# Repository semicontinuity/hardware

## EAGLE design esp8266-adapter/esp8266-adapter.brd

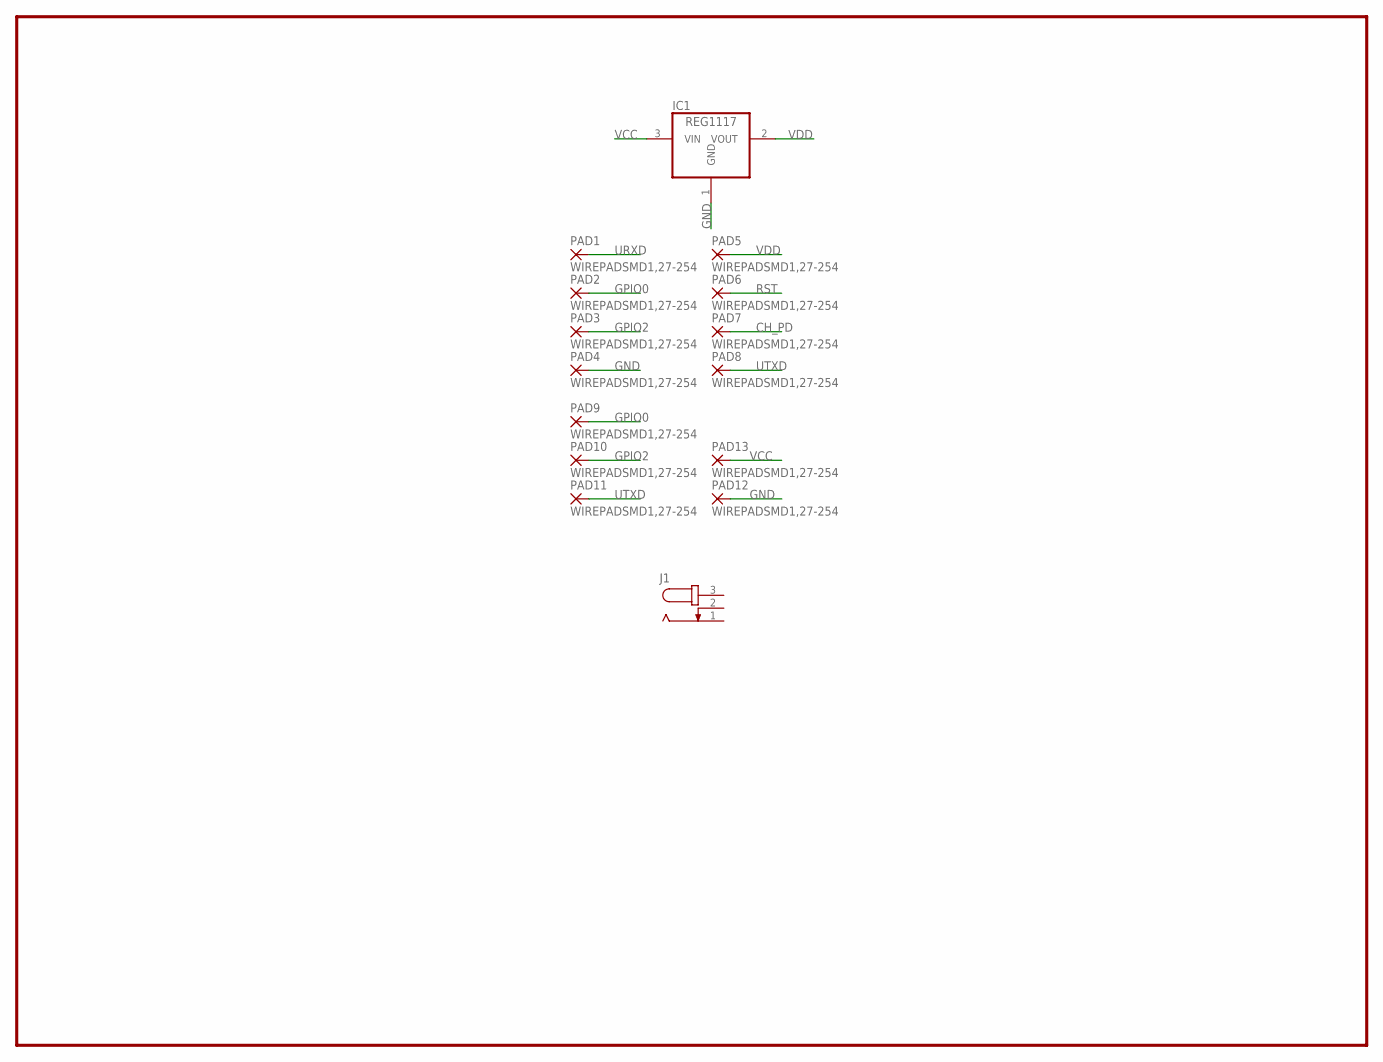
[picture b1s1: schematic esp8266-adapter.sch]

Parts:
IC1: REG1117; SOT223
J1: JACK-PLUG0; SPC4077
PAD1, PAD2, PAD3, PAD4, PAD5, PAD6, PAD7, PAD8, PAD9, PAD10, PAD11, PAD12, PAD13: WIREPADSMD1,27-254; SMD1,27-2,54

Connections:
CH_PD: PAD7.1
GND: IC1.1 (GND), PAD4.1, PAD12.1
GPIO0: PAD2.1, PAD9.1
GPIO2: PAD3.1, PAD10.1
RST: PAD6.1
URXD: PAD1.1
UTXD: PAD8.1, PAD11.1
VCC: IC1.3 (VIN), PAD13.1
VDD: IC1.2 (VOUT), PAD5.1

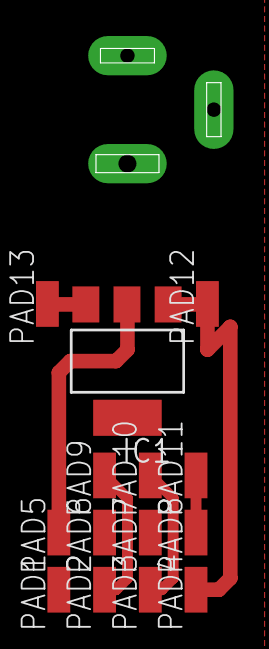
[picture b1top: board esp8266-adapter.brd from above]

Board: 2 copper layers, 15 parts (1 on the bottom side), 6 nets.

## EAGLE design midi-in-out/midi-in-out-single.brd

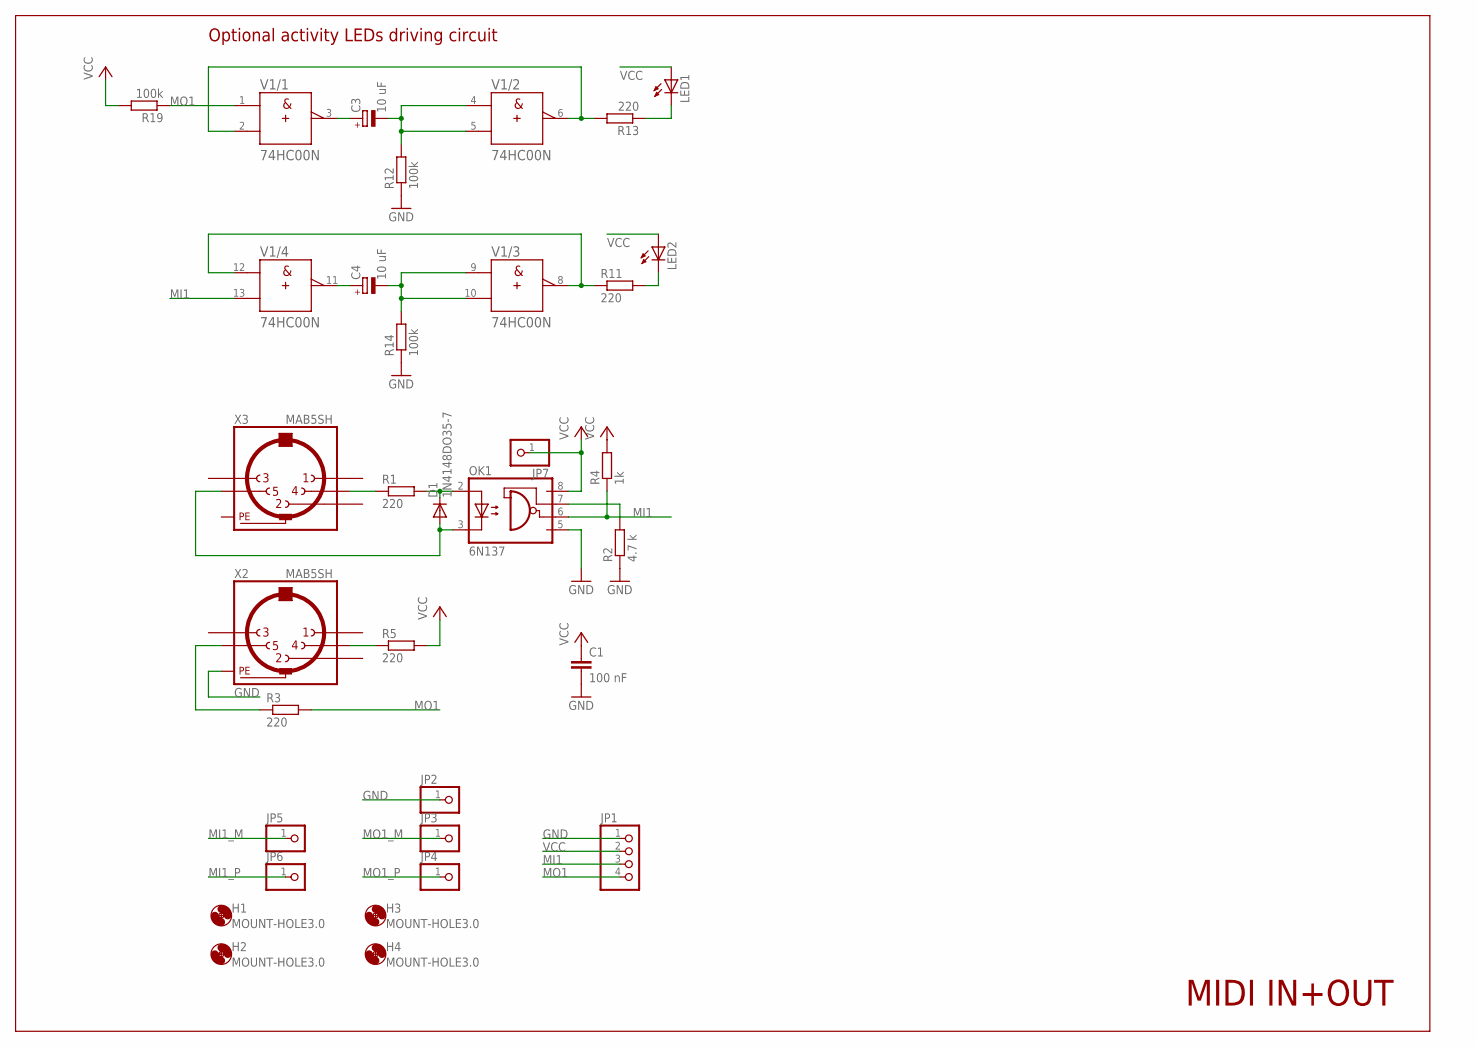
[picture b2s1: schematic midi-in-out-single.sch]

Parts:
C1: 100 nF; C025-024X044
C3, C4: 10 uF; E2,5-5
D1: 1N4148DO35-7; DO35-7
H1, H2, H3, H4: MOUNT-HOLE3.0; 3,0
JP1: PINHD-1X4/90; 1X04/90
JP2, JP3, JP4, JP5, JP6, JP7: PINHD-1X1; 1X01
LED1, LED2: LED3MM
OK1: 6N137; DIL08
R1, R3, R5, R11, R13: 220; 0204/7
R2: 4.7 k; 0204/7
R4: 1k; 0204/7
R12, R14, R19: 100k; 0204/7
V1: 74HC00N; DIL14
X2, X3: MAB5SH

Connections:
GND: C1.2, JP1.1, JP2.1, OK1.5 (GND), R2.1, R12.1, R14.1, V1.7 (-UB), X2.PE, X2.PE@ (PE)
MI1: JP1.3, OK1.6 (VO), R4.1, V1.13 (B)
MI1_M: D1.A, JP5.1, OK1.3 (C), X3.5
MI1_P: JP6.1, R1.1, X3.4
MO1: JP1.4, R3.2, R19.1, V1.1 (A)
MO1_M: JP3.1, R3.1, X2.5
MO1_P: JP4.1, R5.1, X2.4
unnamed: D1.C, OK1.2 (A), R1.2
unnamed: OK1.7 (VE), R2.2
unnamed: LED2.K (C), R11.2
unnamed: LED1.K (C), R13.1
unnamed: C4.+, V1.11 (Y)
unnamed: C3.-, R12.2, V1.4 (A), V1.5 (B)
unnamed: C3.+, V1.3 (Y)
unnamed: R13.2, V1.2 (B), V1.6 (Y)
unnamed: C4.-, R14.2, V1.9 (A), V1.10 (B)
unnamed: R11.1, V1.8 (Y), V1.12 (A)
PE: X3.PE, X3.PE@ (PE)
VCC: C1.1, JP1.2, JP7.1, LED1.A, LED2.A, OK1.8 (VCC), R4.2, R5.2, R19.2, V1.14 (+UB)

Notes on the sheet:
MIDI IN+OUT
Optional activity LEDs driving circuit

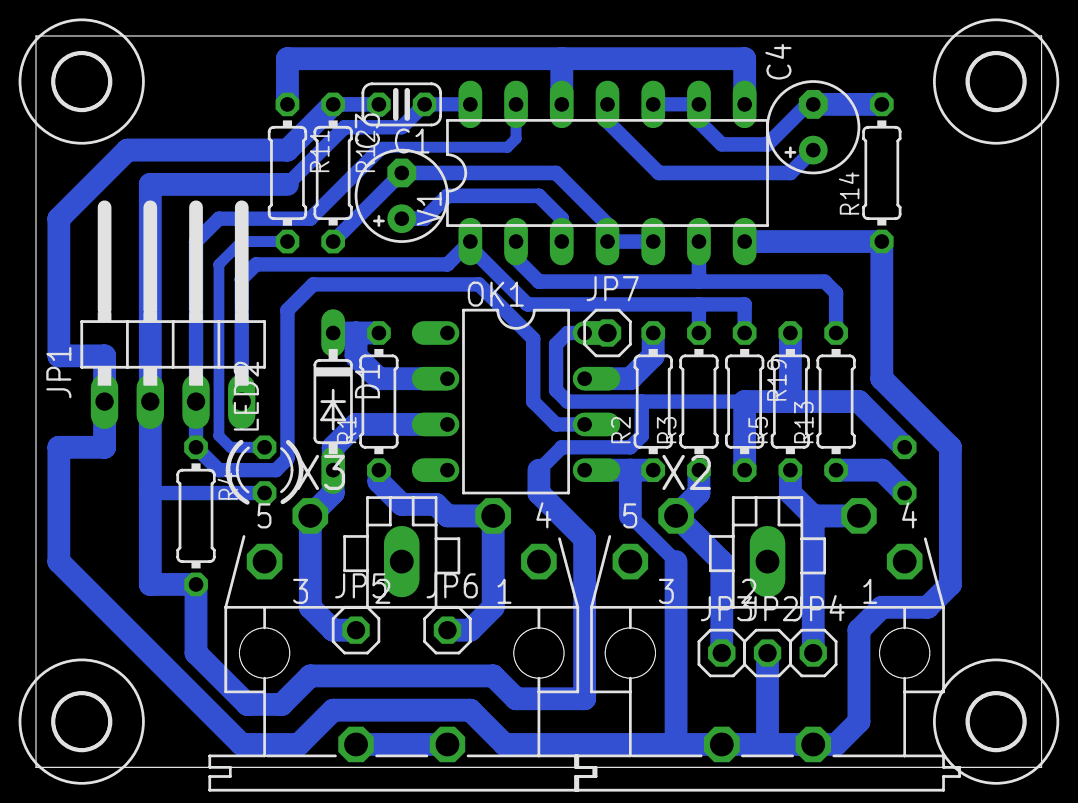
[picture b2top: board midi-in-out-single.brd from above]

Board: 2 copper layers, 55.9 x 40.6 mm, 31 parts (1 on the bottom side), 19 nets.
